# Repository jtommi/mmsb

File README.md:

# Intro

This repository contains different modules and schematics.

## Modules

### [AS3340](AS3340) (not tested)

This is a simple 1V/oct VCO using the AS3340/CEM3340 chip.
Based mostly on [Look Mum No cumpter's project](https://www.lookmumnocomputer.com/projects/#/cem-3340-diy-simple)

I added some things from the AS3340 datasheet.

### [LMNC Attack Release 2.0](LMNC%20Attack%20Release%202.0) (not tested)

A simple envelope generator with Attack and Release or Decay
Schematic drawn from [Look Mum No cumpter's stripboard layout](https://www.lookmumnocomputer.com/projects#/simple-envelope-generator)

### [LMNC Dual VCA](LMNC%20Dual%20VCA) (not tested)

A dual VCA using the AS3360 chip.
Schematic mostly drawn from [Look Mum No cumpter's schematic](https://www.lookmumnocomputer.com/projects#/1181-dual-vca)

## Common

### Power.sch

This is a schematic of the power header common to all modules

## Models

This contains some 3D models like standard eurorack panels, potentiometers, etc.

## Other

### [Stripboard](Other/Stripboard) (not tested)

A stripboard for ordering from PCB manufacturers

### Breadboard.kicad_pcb

A simple arrangement of copper traces respecting breadboard distances.

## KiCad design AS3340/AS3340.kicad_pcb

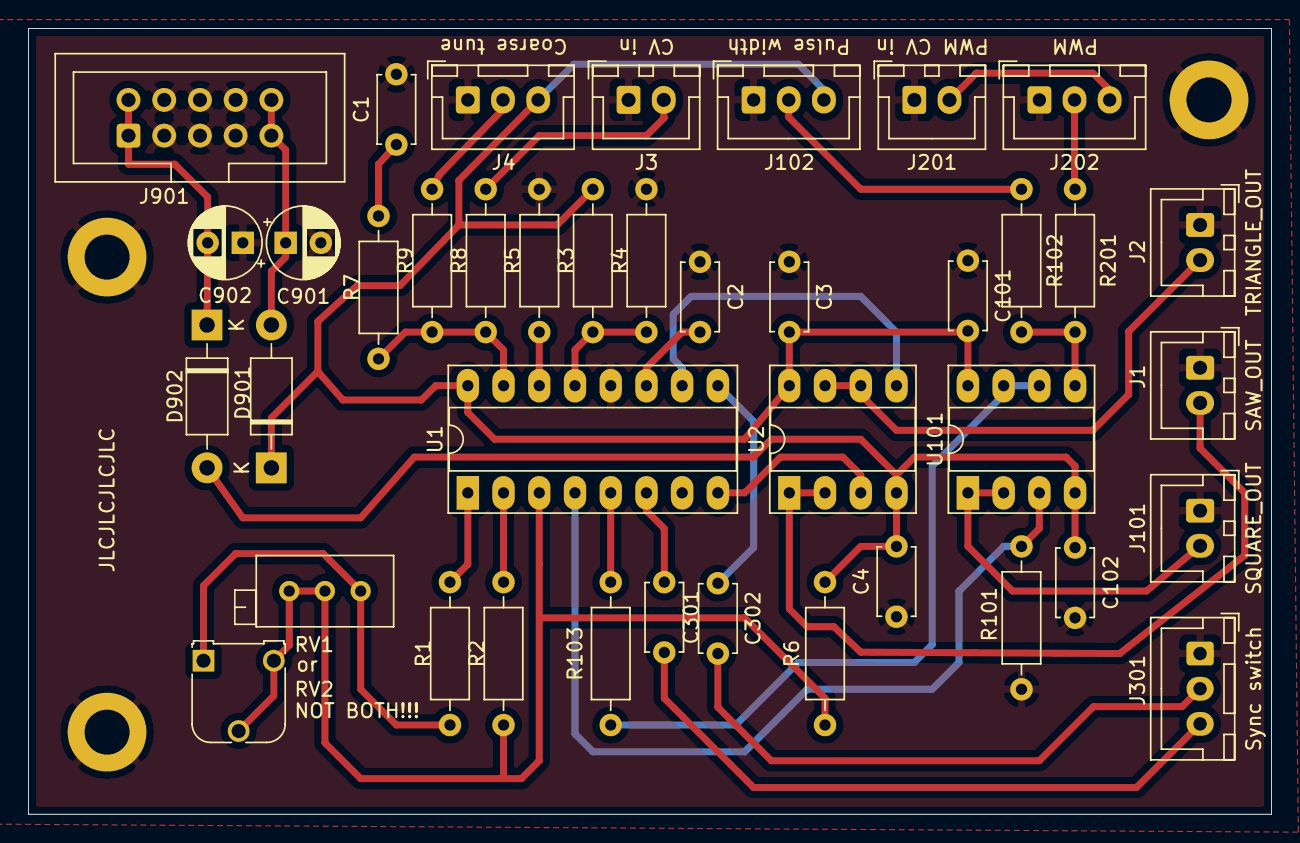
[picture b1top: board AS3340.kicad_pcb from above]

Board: 2 copper layers, 88.4 x 55.9 mm, 40 parts (0 on the bottom side), 32 nets.

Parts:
C1: 10n; C_Disc_D4.7mm_W2.5mm_P5.00mm
C2, C301, C302: 1n; C_Disc_D4.7mm_W2.5mm_P5.00mm
C3, C4, C101, C102: 100n; C_Disc_D4.7mm_W2.5mm_P5.00mm
C901, C902: 10u; CP_Radial_D5.0mm_P2.50mm
D901, D902: 1N5817; D_DO-41_SOD81_P10.16mm_Horizontal
J1: SAW_OUT; JST_XH_B2B-XH-A_1x02_P2.50mm_Vertical
J2: TRIANGLE_OUT; JST_XH_B2B-XH-A_1x02_P2.50mm_Vertical
J3: CV in; JST_XH_B2B-XH-A_1x02_P2.50mm_Vertical
J4: Coarse tune; JST_XH_B3B-XH-A_1x03_P2.50mm_Vertical
J101: SQUARE_OUT; JST_XH_B2B-XH-A_1x02_P2.50mm_Vertical
J102: Pulse width; JST_XH_B3B-XH-A_1x03_P2.50mm_Vertical
J201: PWM CV in; JST_XH_B2B-XH-A_1x02_P2.50mm_Vertical
J202: PWM; JST_XH_B3B-XH-A_1x03_P2.50mm_Vertical
J301: Sync switch; JST_XH_B3B-XH-A_1x03_P2.50mm_Vertical
J901: Eurorack power header; IDC-Header_2x05_P2.54mm_Vertical
R1: 24k; R_Axial_DIN0207_L6.3mm_D2.5mm_P10.16mm_Horizontal
R2: 5k6; R_Axial_DIN0207_L6.3mm_D2.5mm_P10.16mm_Horizontal
R3: 1M5; R_Axial_DIN0207_L6.3mm_D2.5mm_P10.16mm_Horizontal
R4, R7: 470; R_Axial_DIN0207_L6.3mm_D2.5mm_P10.16mm_Horizontal
R5: 1k8; R_Axial_DIN0207_L6.3mm_D2.5mm_P10.16mm_Horizontal
R6: 620; R_Axial_DIN0207_L6.3mm_D2.5mm_P10.16mm_Horizontal
R8, R9, R102, R201: 100k; R_Axial_DIN0207_L6.3mm_D2.5mm_P10.16mm_Horizontal
R101: 10k; R_Axial_DIN0207_L6.3mm_D2.5mm_P10.16mm_Horizontal
R103: 470k; R_Axial_DIN0207_L6.3mm_D2.5mm_P10.16mm_Horizontal
RV1: 10k; Potentiometer_Bourns_3296X_Horizontal
RV2: 10k; Potentiometer_Runtron_RM-065_Vertical
U1: AS3340; DIP-16_W7.62mm_Socket_LongPads
U2, U101: TL072; DIP-8_W7.62mm_Socket_LongPads

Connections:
+12V: C3.2, C101.2, D901.1, J4.3, J102.3, R3.1, U1.16, U2.8, U101.8
-12V: C4.2, C102.2, D902.2, R6.2, U2.4, U101.4
/CV: R7.2, R8.2, R9.2, U1.15
/PWM: R103.1, U1.5
/SAW: U1.8, U2.3
/SQUARE: R101.1, U1.4, U101.3
/TRIANGLE: U1.10, U2.5
GND: C1.2, C2.2, C3.1, C4.1, C101.1, C102.1, C901.2, C902.1, J1.1, J2.1, J3.1, J4.1, J101.1, J102.1, J201.1, J202.1, J301.1, J901.3, J901.4, J901.5, J901.6, J901.7, J901.8, R4.1, R5.2, R101.2, U1.12
unnamed: C1.1, R7.1
unnamed: C2.1, U1.11
unnamed: C301.1, U1.6
unnamed: C301.2, J301.3
unnamed: C302.1, U1.9
unnamed: C302.2, J301.2
unnamed: C901.1, D901.2, J901.9, J901.10
unnamed: C902.2, D902.1, J901.1, J901.2
unnamed: J1.2, U2.1, U2.2
unnamed: J2.2, U2.6, U2.7
unnamed: J3.2, R8.1
unnamed: J4.2, R9.1
unnamed: J101.2, U101.1, U101.2
unnamed: J102.2, R102.1
unnamed: J201.2, J202.3
unnamed: J202.2, R201.1
unnamed: R1.1, U1.1
unnamed: R1.2, RV1.1, RV2.1
unnamed: R2.1, R6.1, RV1.2, RV1.3, RV2.2, RV2.3, U1.3
unnamed: R2.2, U1.2
unnamed: R3.2, R4.2, U1.13
unnamed: R5.1, U1.14
unnamed: R102.2, R201.2, U101.5
unnamed: R103.2, U101.6, U101.7

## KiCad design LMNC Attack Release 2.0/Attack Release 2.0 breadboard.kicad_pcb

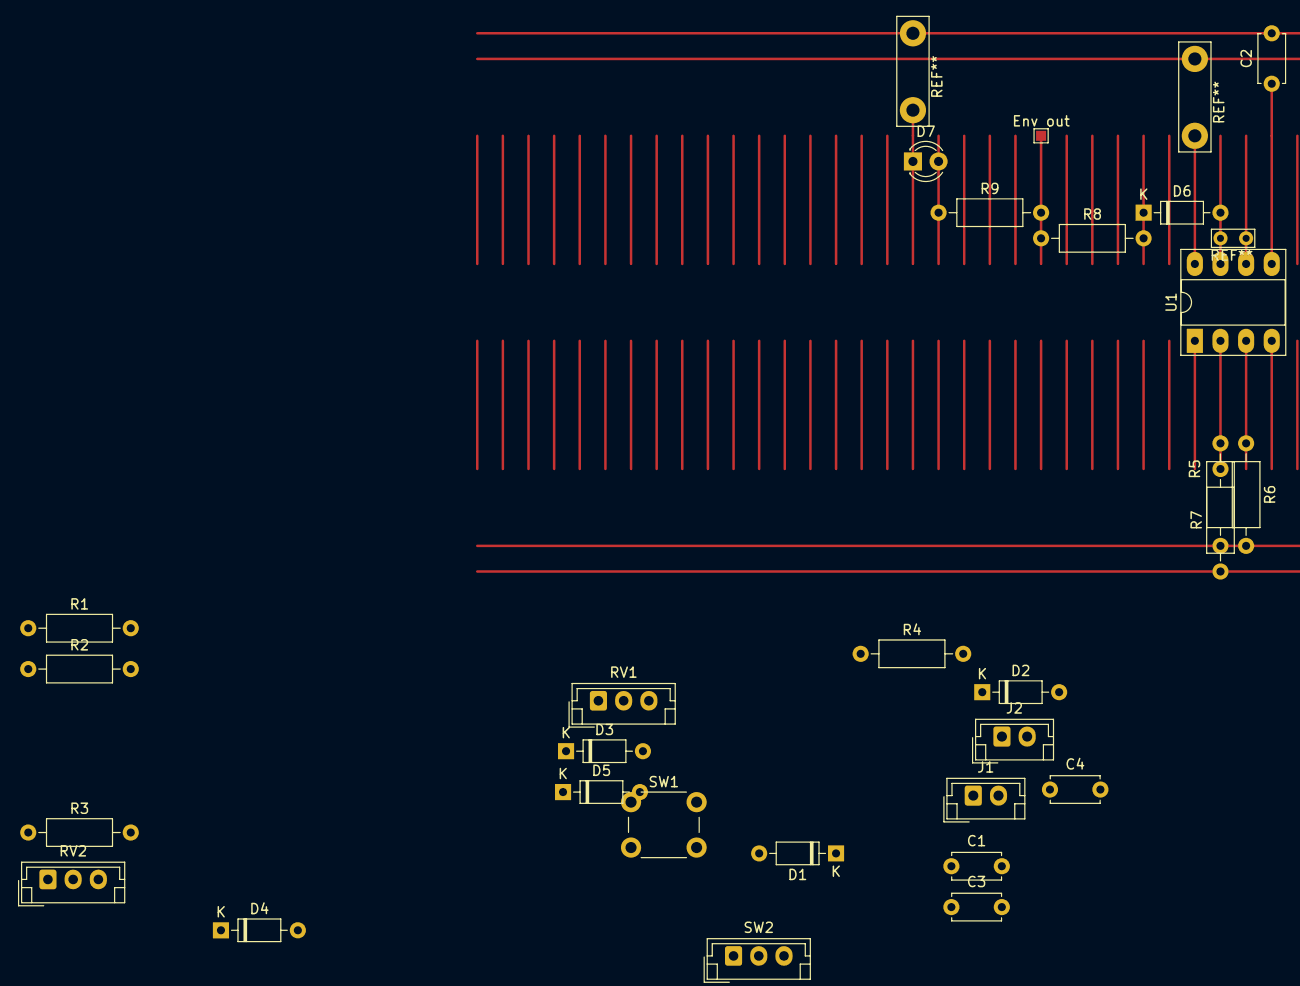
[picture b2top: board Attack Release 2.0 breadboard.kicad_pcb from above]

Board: 2 copper layers, 28 parts (0 on the bottom side), 19 nets.

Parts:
C1: 10n; C_Disc_D4.7mm_W2.5mm_P5.00mm
C2: 1µ; C_Disc_D4.7mm_W2.5mm_P5.00mm
C3, C4: 100n; C_Disc_D4.7mm_W2.5mm_P5.00mm
D1, D2, D3, D4, D5, D6: 1N4148; D_DO-35_SOD27_P7.62mm_Horizontal
D7: LED; LED_D3.0mm
Env out: TestPoint_Pad_1.0x1.0mm
J1: Gate in; JST_EH_B2B-EH-A_1x02_P2.50mm_Vertical
J2: Envelope out; JST_EH_B2B-EH-A_1x02_P2.50mm_Vertical
R1, R3, R4, R6: 100k; R_Axial_DIN0207_L6.3mm_D2.5mm_P10.16mm_Horizontal
R2, R7: 47k; R_Axial_DIN0207_L6.3mm_D2.5mm_P10.16mm_Horizontal
R5: 10k; R_Axial_DIN0207_L6.3mm_D2.5mm_P10.16mm_Horizontal
R8, R9: 1k; R_Axial_DIN0207_L6.3mm_D2.5mm_P10.16mm_Horizontal
RV1: Attack; JST_EH_B3B-EH-A_1x03_P2.50mm_Vertical
RV2: Release; JST_EH_B3B-EH-A_1x03_P2.50mm_Vertical
SW1: SW_Push; SW_PUSH_6mm
SW2: SW_SPDT; JST_EH_B3B-EH-A_1x03_P2.50mm_Vertical
U1: TL072; DIP-8_W7.62mm_Socket_LongPads

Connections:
+12V: C3.2, R7.1, SW1.1, U1.8
-12V: C4.1, U1.4
GND: C2.2, C3.1, C4.2, D2.2, D7.1, R4.1, R5.2, R6.2
unnamed: C1.1, R4.2, SW2.1
unnamed: C1.2, R1.2, R2.2
unnamed: C2.1, RV1.1, RV1.2, RV2.1, RV2.2, U1.5
unnamed: D1.1, SW1.2, SW2.2
unnamed: D2.1, R2.1
unnamed: D3.1, R6.1, U1.3
unnamed: D3.2, R3.1
unnamed: D4.1, RV1.3
unnamed: D4.2, D5.1, U1.1
unnamed: D5.2, RV2.3
unnamed: D6.1, R8.2
unnamed: D6.2, U1.6, U1.7
unnamed: D7.2, R9.1
unnamed: R8.1, R9.2
unnamed: R1.1, R3.2, SW2.3
unnamed: R5.1, R7.2, U1.2

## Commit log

2021-01-06 Added theremin
2021-01-10 Final stripboard and AS3340
2021-01-17 Added stripboard
2021-01-17 Added common power header
2021-01-17 Cleanup
2021-01-17 Added breadboard
2021-01-17 Added Attack Release 2.0
2021-01-17 Added Dual VCA
2021-01-17 Added Readme
2021-01-23 Corrected value. Rearranged silkscreen
2021-01-24 Corrected error in the circuit
